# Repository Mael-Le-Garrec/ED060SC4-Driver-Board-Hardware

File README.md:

# ED060SC4 Driver Board

This projects intends to be a SPI driver board for the E-Ink display screen
`ED060SC4`.

This project is still under development, you can have a look at the schematics,
the PCB or the components, but it's not finished and will likely change!

## Schematics

The board is centered around 3 building blocks:

- ED060SC4, EPD screen
- STM32F103C8T6, microcontroller used to drive the screen
- TPS65185, used to generate the different rails required

The schematics can be found in [pdf](./outputs/schematics/ED060SC4_SPI_driver_board.pdf).

## Interactive Board

The PCB, nets and BOM can be seen in an [interactive html format](http://htmlpreview.github.io/?https://raw.githubusercontent.com/Mael-Le-Garrec/ED060SC4-Driver-Board-Hardware/master/outputs/html/ibom.html).

## Gerbers

The gerber files are available in a [zip archive](./outputs/gerbers/gerbers.zip)
ready to be sent for manufacturing.

## Images

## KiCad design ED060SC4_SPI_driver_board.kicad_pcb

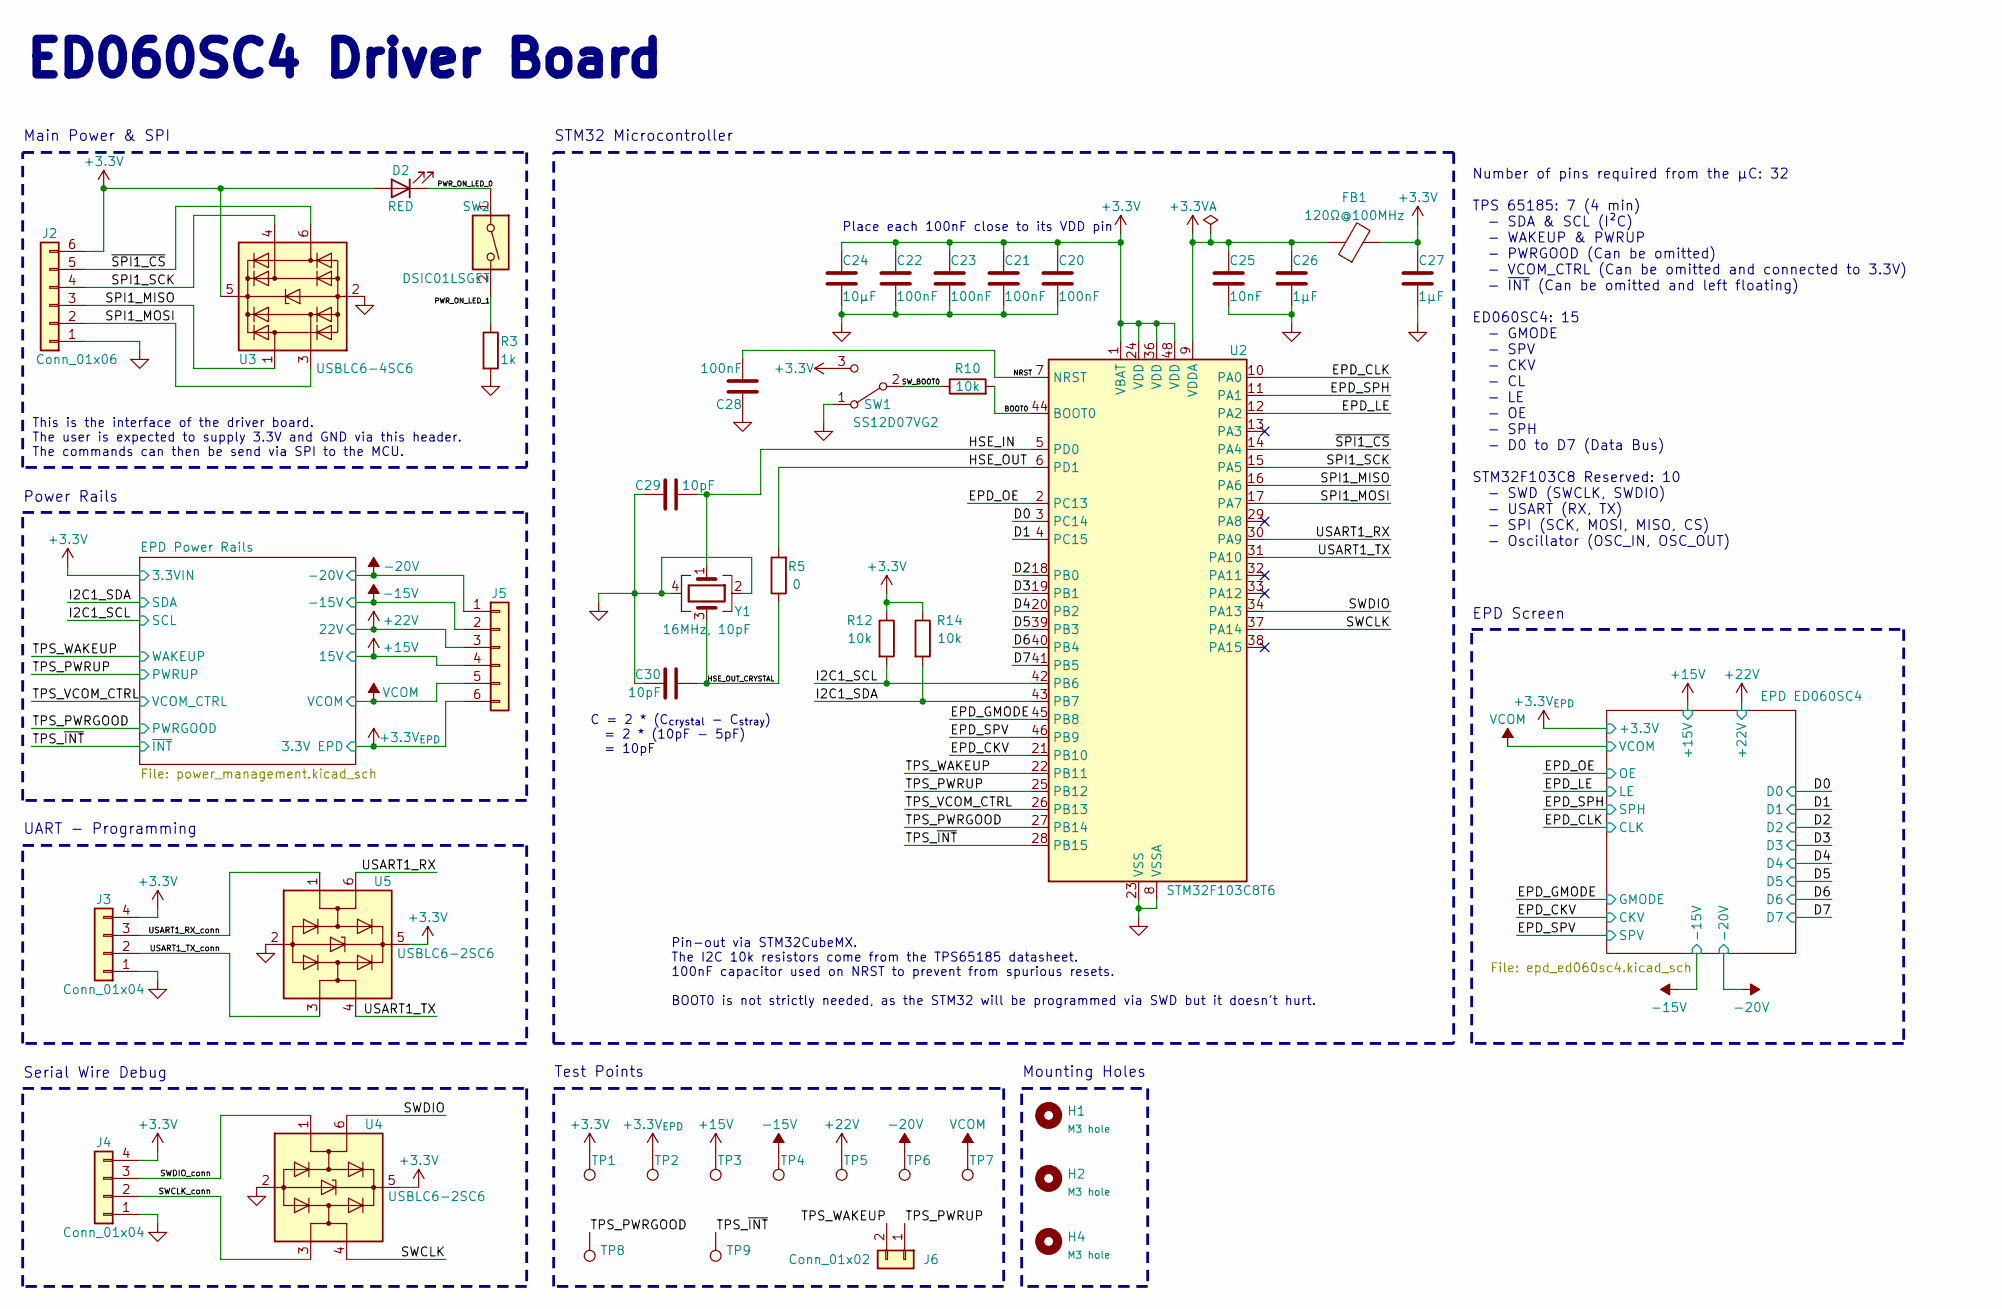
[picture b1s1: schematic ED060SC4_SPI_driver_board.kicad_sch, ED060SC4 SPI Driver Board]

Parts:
C20, C21, C22, C23, C28: 100nF; C_0603_1608Metric; LCSC Part # C1591
C24: 10µF; C_0603_1608Metric; LCSC Part # C85713
C25: 10nF; C_0603_1608Metric; LCSC Part # C1589
C26, C27: 1µF; C_0603_1608Metric; LCSC Part # C5673
C29, C30: 10pF; C_0603_1608Metric; LCSC Part # C1634
D2: RED; LED_0603_1608Metric; LCSC Part # C434419
FB1: 120Ω@100MHz; R_0603_1608Metric; LCSC Part # C14709
H1, H2, H4: M3 hole; MountingHole_2.2mm_M2
J2: Conn_01x06; PinHeader_1x06_P2.54mm_Vertical
J3, J4: Conn_01x04; PinSocket_1x04_P2.54mm_Vertical
J5: Conn_01x06; PinSocket_1x06_P2.54mm_Vertical
J6: Conn_01x02; PinSocket_1x02_P2.54mm_Vertical
R3: 1k; R_0603_1608Metric; LCSC Part # C22548
R5: 0; R_0603_1608Metric; LCSC Part # C103196
R10, R12, R14: 10k; R_0603_1608Metric; LCSC Part # C98220
SW1: SS12D07VG2; SW_SS12D07VG4; LCSC Part # C2939724
SW2: DSIC01LSGET; LCSC Part # C54948
TP1, TP2, TP3, TP4, TP5, TP6, TP7, TP8, TP9: TestPoint; TestPoint_Pad_D1.0mm
U2: STM32F103C8T6; LQFP-48_7x7mm_P0.5mm; LCSC Part # C8734
U3: USBLC6-4SC6; SOT-23-6; LCSC Part # C5197386
U4, U5: USBLC6-2SC6; SOT-23-6; LCSC Part # C2827654
Y1: 16MHz, 10pF; Crystal_SMD_3225-4Pin_3.2x2.5mm; LCSC Part # C112972

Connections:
+3.3V: C20.1, C21.1, C22.1, C23.1, C24.1, C27.1, D2.2 (A), FB1.2, J2.6, J3.4, J4.4, R12.1, R14.1, SW1.3 (C), TP1.1, U2.1 (VBAT), U2.24 (VDD), U2.36 (VDD), U2.48 (VDD), U3.5 (VBUS), U4.5 (VBUS), U5.5 (VBUS); also elsewhere on the board
+3.3VA: C25.1, C26.1, FB1.1, U2.9 (VDDA)
+15V: J5.4, TP3.1; also elsewhere on the board
+22V: J5.3, TP5.1; also elsewhere on the board
-15V: J5.2, TP4.1; also elsewhere on the board
-20V: J5.1, TP6.1; also elsewhere on the board
/BOOT0: R10.2, U2.44 (BOOT0)
/D0: U2.3 (PC14); also elsewhere on the board
/D1: U2.4 (PC15); also elsewhere on the board
/D2: U2.18 (PB0); also elsewhere on the board
/D3: U2.19 (PB1); also elsewhere on the board
/D4: U2.20 (PB2); also elsewhere on the board
/D5: U2.39 (PB3); also elsewhere on the board
/D6: U2.40 (PB4); also elsewhere on the board
/D7: U2.41 (PB5); also elsewhere on the board
/EPD_CKV: U2.21 (PB10); also elsewhere on the board
/EPD_CLK: U2.10 (PA0); also elsewhere on the board
/EPD_GMODE: U2.45 (PB8); also elsewhere on the board
/EPD_LE: U2.12 (PA2); also elsewhere on the board
/EPD_OE: U2.2 (PC13); also elsewhere on the board
/EPD_SPH: U2.11 (PA1); also elsewhere on the board
/EPD_SPV: U2.46 (PB9); also elsewhere on the board
/HSE_IN: C29.2, U2.5 (PD0), Y1.1
/HSE_OUT: R5.2, U2.6 (PD1)
/HSE_OUT_CRYSTAL: C30.2, R5.1, Y1.3
/I2C1_SCL: R12.2, U2.42 (PB6); also elsewhere on the board
/I2C1_SDA: R14.2, U2.43 (PB7); also elsewhere on the board
/NRST: C28.2, U2.7 (NRST)
/PWR_ON_LED_0: D2.1 (K), SW2.1
/PWR_ON_LED_1: R3.1, SW2.2
/SPI1_MISO: J2.3, U2.16 (PA6), U3.1 (I/O1)
/SPI1_MOSI: J2.2, U2.17 (PA7), U3.3 (I/O2)
/SPI1_SCK: J2.4, U2.15 (PA5), U3.4 (I/O3)
/SWCLK: U2.37 (PA14), U4.4 (I/O2)
/SWCLK_conn: J4.2, U4.3 (I/O2)
/SWDIO: U2.34 (PA13), U4.6 (I/O1)
/SWDIO_conn: J4.3, U4.1 (I/O1)
/SW_BOOT0: R10.1, SW1.2 (B)
/TPS_PWRGOOD: TP8.1, U2.27 (PB14); also elsewhere on the board
/TPS_PWRUP: J6.1, U2.25 (PB12); also elsewhere on the board
/TPS_VCOM_CTRL: U2.26 (PB13); also elsewhere on the board
/TPS_WAKEUP: J6.2, U2.22 (PB11); also elsewhere on the board
/TPS_~INT: TP9.1, U2.28 (PB15); also elsewhere on the board
/USART1_RX: U2.30 (PA9), U5.6 (I/O1)
/USART1_RX_conn: J3.3, U5.1 (I/O1)
/USART1_TX: U2.31 (PA10), U5.4 (I/O2)
/USART1_TX_conn: J3.2, U5.3 (I/O2)
/~SPI1_CS: J2.5, U2.14 (PA4), U3.6 (I/O4)
GND: C20.2, C21.2, C22.2, C23.2, C24.2, C25.2, C26.2, C27.2, C28.1, C29.1, C30.1, J2.1, J3.1, J4.1, R3.2, SW1.1 (A), U2.8 (VSSA), U2.23 (VSS), U2.35 (VSS), U2.47 (VSS), U3.2 (GND), U4.2 (GND), U5.2 (GND), Y1.2, Y1.4; also elsewhere on the board

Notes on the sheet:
Number of pins required from the µC: 32 TPS 65185: 7 (4 min) - SDA & SCL (I²C) - WAKEUP & PWRUP - PWRGOOD (Can be omitted) - VCOM_CTRL (Can be omitted and connected to 3.3V) - ~{INT} (Can be omitted and left floating) ED060SC4: 15 - GMODE - SPV - CKV - CL - LE - OE - SPH - D0 to D7 (Data Bus) STM32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
Pin-out via STM32CubeMX. The I2C 10k resistors come from the TPS65185 datasheet. 100nF capacitor used on NRST to prevent from spurious resets. BOOT0 is not strictly needed, as the STM32 will be programmed via SWD but it doesn't hurt.
EPD Screen
STM32 Microcontroller
Main Power & SPI
Power Rails
This is the interface of the driver board. The user is expected to supply 3.3V and GND via this header. The commands can then be send via SPI to the MCU.
Place each 100nF close to its VDD pin
ED060SC4 Driver Board
Serial Wire Debug
Test Points
C = 2 * (C_{crystal} - C_{stray}) = 2 * (10pF - 5pF) = 10pF
UART - Programming
Mounting Holes

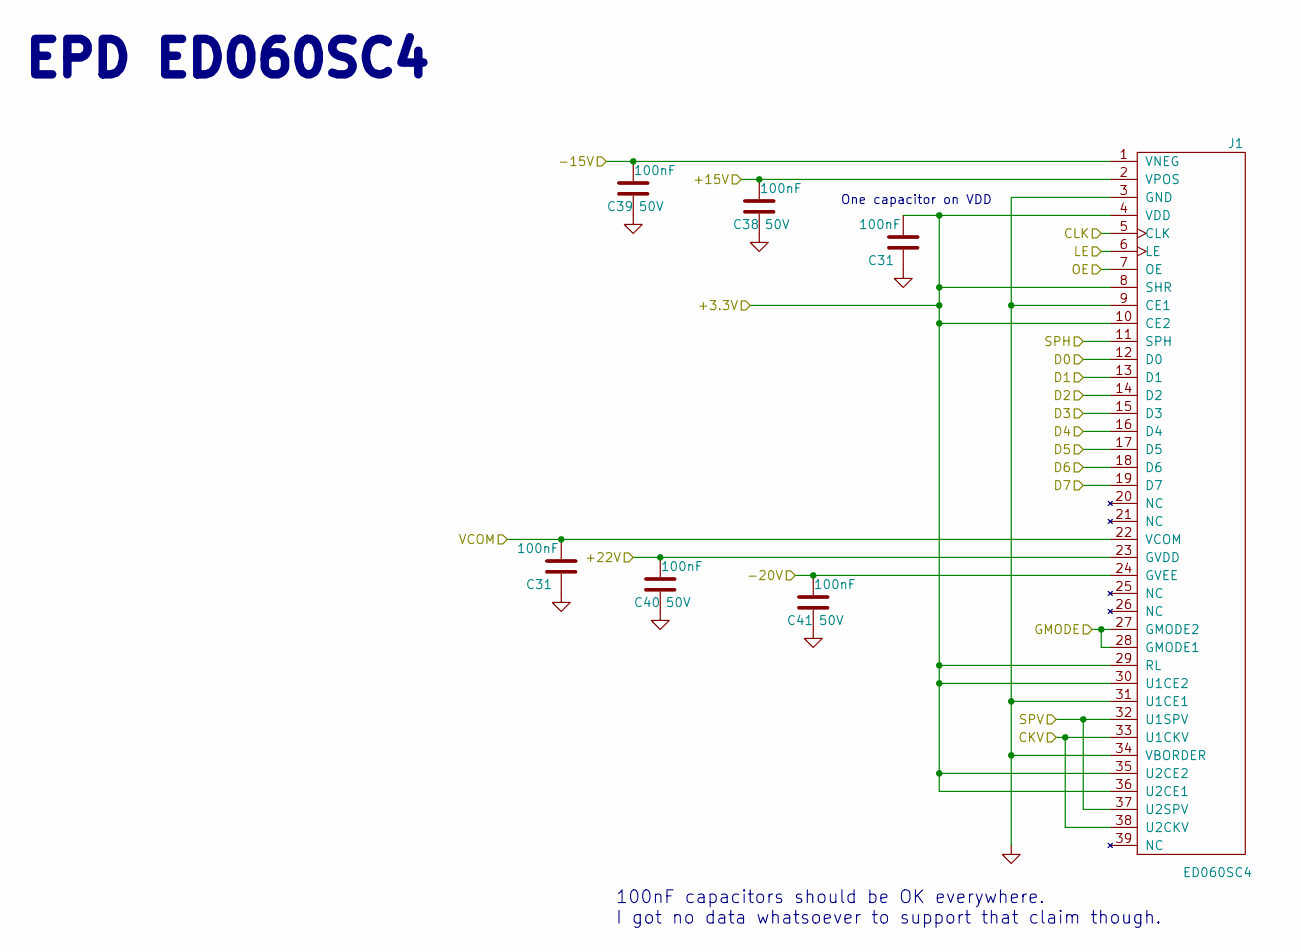
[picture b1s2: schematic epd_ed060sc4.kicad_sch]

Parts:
C31: 100nF; C_0603_1608Metric; LCSC Part # C1591
C38, C39, C40, C41: 100nF; C_0603_1608Metric; Voltage 50V; LCSC Part # C1591
J1: ED060SC4; HRS_FH26W-39S-0.3SHW(60); LCSC Part # C92280

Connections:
+15V: C38.1, J1.2 (VPOS); also elsewhere on the board
+22V: C40.1, J1.23 (GVDD); also elsewhere on the board
-15V: C39.1, J1.1 (VNEG); also elsewhere on the board
-20V: C41.1, J1.24 (GVEE); also elsewhere on the board
/D0: J1.12 (D0); also elsewhere on the board
/D1: J1.13 (D1); also elsewhere on the board
/D2: J1.14 (D2); also elsewhere on the board
/D3: J1.15 (D3); also elsewhere on the board
/D4: J1.16 (D4); also elsewhere on the board
/D5: J1.17 (D5); also elsewhere on the board
/D6: J1.18 (D6); also elsewhere on the board
/D7: J1.19 (D7); also elsewhere on the board
/EPD_CKV: J1.33 (U1CKV), J1.38 (U2CKV); also elsewhere on the board
/EPD_CLK: J1.5 (CLK); also elsewhere on the board
/EPD_GMODE: J1.27 (GMODE2), J1.28 (GMODE1); also elsewhere on the board
/EPD_LE: J1.6 (LE); also elsewhere on the board
/EPD_OE: J1.7 (OE); also elsewhere on the board
/EPD_SPH: J1.11 (SPH); also elsewhere on the board
/EPD_SPV: J1.32 (U1SPV), J1.37 (U2SPV); also elsewhere on the board
GND: C31.2, C38.2, C39.2, C40.2, C41.2, J1.3 (GND), J1.9 (CE1), J1.31 (U1CE1), J1.34 (VBORDER); also elsewhere on the board

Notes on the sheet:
100nF capacitors should be OK everywhere. I got no data whatsoever to support that claim though.
One capacitor on VDD
EPD ED060SC4

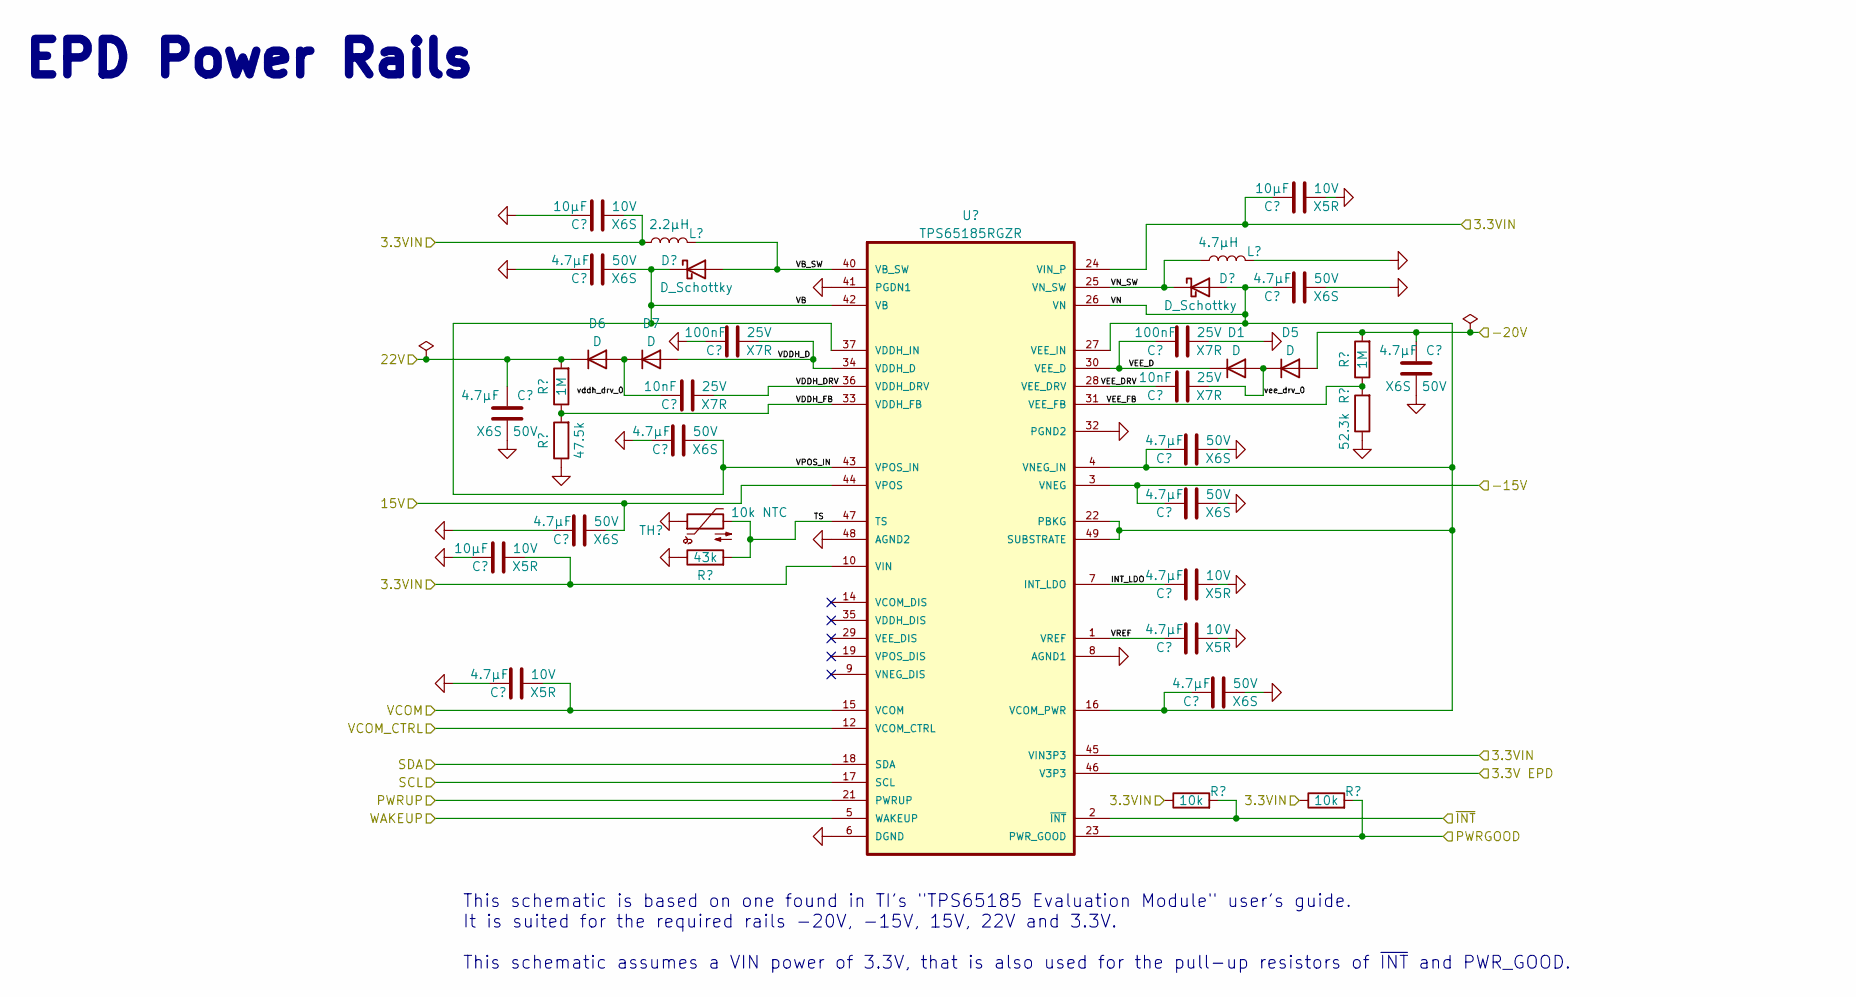
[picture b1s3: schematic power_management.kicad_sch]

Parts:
C1, C4, C6, C8, C10, C11, C14, C18, C19: 4.7µF; C_0805_2012Metric; Voltage 50V; LCSC Part # C98192
C2, C5, C17: 10µF; C_0603_1608Metric; Voltage 10V; LCSC Part # C85713
C3, C12, C13: 4.7µF; C_0805_2012Metric; Voltage 10V; LCSC Part # C98192
C7, C15: 10nF; C_0603_1608Metric; Voltage 25V; LCSC Part # C1589
C9, C16: 100nF; C_0603_1608Metric; Voltage 25V; LCSC Part # C1591
D1, D5, D6, D7: D; D_SOD-123; LCSC Part # C82544
D3, D4: D_Schottky; D_SOD-123; LCSC Part # C82544
L1: 2.2µH; TDK_VLS252015ET-2R2M; LCSC Part # C136232
L2: 4.7µH; L_Taiyo-Yuden_NR-40xx; LCSC Part # C92936
R1, R8: 1M; R_0603_1608Metric; LCSC Part # C105578
R2: 47.5k; R_0603_1608Metric; LCSC Part # C137715
R4: 43k; R_0603_1608Metric; LCSC Part # C137719
R6, R7: 10k; R_0603_1608Metric; LCSC Part # C98220
R9: 52.3k; R_0603_1608Metric; LCSC Part # C185323
TH1: 10k NTC; R_0603_1608Metric; LCSC Part # C13564
U1: TPS65185RGZR; QFN50P700X700X100-49N; LCSC Part # C139291

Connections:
+3.3V: C2.1, C5.2, C17.2, L1.1, R6.1, R7.1, U1.10 (VIN), U1.24 (VIN_P), U1.45 (VIN3P3); also elsewhere on the board
+15V: C4.1, U1.44 (VPOS); also elsewhere on the board
+22V: C1.2, D6.1 (K), R1.2; also elsewhere on the board
-15V: C11.1, U1.3 (VNEG); also elsewhere on the board
-20V: C19.2, D5.2 (A), R8.2; also elsewhere on the board
/EPD Power Rails/INT_LDO: C12.1, U1.7 (INT_LDO)
/EPD Power Rails/TS: R4.2, TH1.2, U1.47 (TS)
/EPD Power Rails/VB: C6.2, C8.2, D3.1 (K), U1.37 (VDDH_IN), U1.42 (VB), U1.43 (VPOS_IN)
/EPD Power Rails/VB_SW: D3.2 (A), L1.2, U1.40 (VB_SW)
/EPD Power Rails/VDDH_D: C9.2, D7.2 (A), U1.34 (VDDH_D)
/EPD Power Rails/VDDH_DRV: C7.2, U1.36 (VDDH_DRV)
/EPD Power Rails/VDDH_FB: R1.1, R2.2, U1.33 (VDDH_FB)
/EPD Power Rails/VEE_D: C16.2, D1.1 (K), U1.30 (VEE_D)
/EPD Power Rails/VEE_DRV: C15.1, U1.28 (VEE_DRV)
/EPD Power Rails/VEE_FB: R8.1, R9.2, U1.31 (VEE_FB)
/EPD Power Rails/VN: C10.1, C14.1, C18.2, D4.2 (A), U1.4 (VNEG_IN), U1.16 (VCOM_PWR), U1.22 (PBKG), U1.26 (VN), U1.27 (VEE_IN), U1.49 (SUBSTRATE)
/EPD Power Rails/VN_SW: D4.1 (K), L2.2, U1.25 (VN_SW)
/EPD Power Rails/VREF: C13.1, U1.1 (VREF)
/EPD Power Rails/vddh_drv_0: C7.1, D6.2 (A), D7.1 (K)
/EPD Power Rails/vee_drv_0: C15.2, D1.2 (A), D5.1 (K)
/I2C1_SCL: U1.17 (SCL); also elsewhere on the board
/I2C1_SDA: U1.18 (SDA); also elsewhere on the board
/TPS_PWRGOOD: R7.2, U1.23 (PWR_GOOD); also elsewhere on the board
/TPS_PWRUP: U1.21 (PWRUP); also elsewhere on the board
/TPS_VCOM_CTRL: U1.12 (VCOM_CTRL); also elsewhere on the board
/TPS_WAKEUP: U1.5 (WAKEUP); also elsewhere on the board
/TPS_~INT: R6.2, U1.2 (~INT); also elsewhere on the board
GND: C1.1, C2.2, C3.2, C4.2, C5.1, C6.1, C8.1, C9.1, C10.2, C11.2, C12.2, C13.2, C14.2, C16.1, C17.1, C18.1, C19.1, L2.1, R2.1, R4.1, R9.1, TH1.1, U1.6 (DGND), U1.8 (AGND1), U1.32 (PGND2), U1.41 (PGDN1), U1.48 (AGND2); also elsewhere on the board

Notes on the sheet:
This schematic is based on one found in TI's "TPS65185 Evaluation Module" user's guide. It is suited for the required rails -20V, -15V, 15V, 22V and 3.3V. This schematic assumes a VIN power of 3.3V, that is also used for the pull-up resistors of ~{INT} and PWR_GOOD.
EPD Power Rails

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
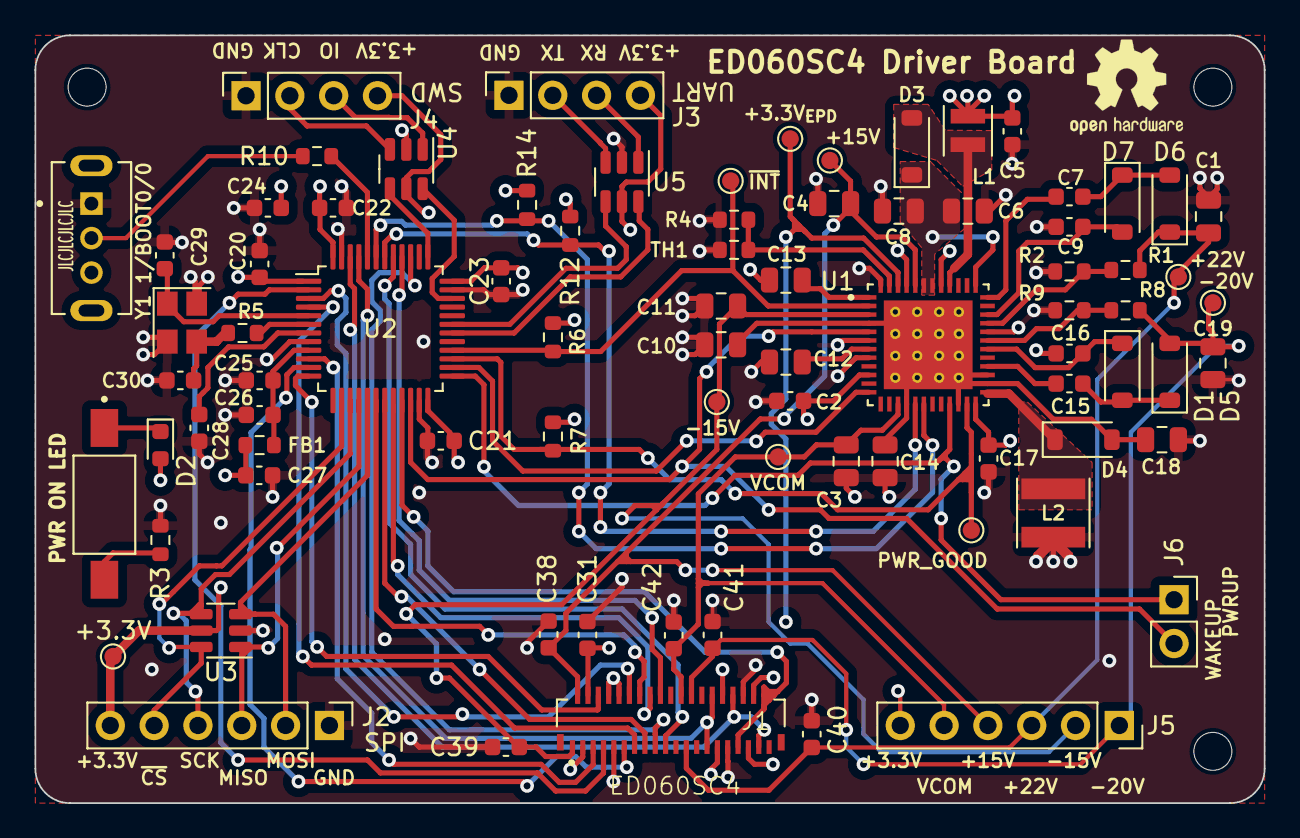
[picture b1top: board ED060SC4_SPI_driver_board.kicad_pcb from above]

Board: 4 copper layers, 71.2 x 44.5 mm, 85 parts (0 on the bottom side), 66 nets.

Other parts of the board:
C42: 100nF; C_0603_1608Metric

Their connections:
GND: C42.2; also elsewhere on the board

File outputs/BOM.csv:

"Reference","Value","Footprint","LCSC Part #","Type","Voltage","Qty"
"C1, C4, C6, C8, C10, C11, C14, C18, C19","4.7µF","Capacitor_SMD:C_0805_2012Metric","C98192","X6S","50V","9"
"C2, C17","10µF","Capacitor_SMD:C_0603_1608Metric","C85713","X5R","10V","2"
"C3, C12, C13","4.7µF","Capacitor_SMD:C_0805_2012Metric","C98192","X5R","10V","3"
"C5","10µF","Capacitor_SMD:C_0603_1608Metric","C85713","X6S","10V","1"
"C7, C15","10nF","Capacitor_SMD:C_0603_1608Metric","C1589","X7R","25V","2"
"C9, C16","100nF","Capacitor_SMD:C_0603_1608Metric","C1591","X7R","25V","2"
"C20-C23, C28, C31, C42","100nF","Capacitor_SMD:C_0603_1608Metric","C1591","","","7"
"C24","10µF","Capacitor_SMD:C_0603_1608Metric","C85713","","","1"
"C25","10nF","Capacitor_SMD:C_0603_1608Metric","C1589","","","1"
"C26, C27","1µF","Capacitor_SMD:C_0603_1608Metric","C5673","","","2"
"C29, C30","10pF","Capacitor_SMD:C_0603_1608Metric","C1634","","","2"
"C38-C41","100nF","Capacitor_SMD:C_0603_1608Metric","C1591","","50V","4"
"D1, D5-D7","D","Diode_SMD:D_SOD-123","C82544","","","4"
"D2","RED","LED_SMD:LED_0603_1608Metric","C82544","","","1"
"D3, D4","D_Schottky","Diode_SMD:D_SOD-123","C82544","","","2"
"FB1","120Ω@100MHz","Resistor_SMD:R_0603_1608Metric","C14709","","","1"
"H1, H2, H4","M3 hole","MountingHole:MountingHole_2.2mm_M2","","","","3"
"J1","ED060SC4","local_lib:HRS_FH26W-39S-0.3SHW(60)","C92280","","","1"
"J2","Conn_01x06","Connector_PinHeader_2.54mm:PinHeader_1x06_P2.54mm_Vertical","","","","1"
"J3, J4","Conn_01x04","Connector_PinSocket_2.54mm:PinSocket_1x04_P2.54mm_Vertical","","","","2"
"J5","Conn_01x06","Connector_PinSocket_2.54mm:PinSocket_1x06_P2.54mm_Vertical","","","","1"
"J6","Conn_01x02","Connector_PinSocket_2.54mm:PinSocket_1x02_P2.54mm_Vertical","","","","1"
"L1","2.2µH","local_lib:TDK_VLS252015ET-2R2M","C136232","","","1"
"L2","4.7µH","Inductor_SMD:L_Taiyo-Yuden_NR-40xx","C92936","","","1"
"R1, R8","1M","Resistor_SMD:R_0603_1608Metric","C105578","","","2"
"R2","47.5k","Resistor_SMD:R_0603_1608Metric","C137715","","","1"
"R3","1k","Resistor_SMD:R_0603_1608Metric","C22548","","","1"
"R4","43k","Resistor_SMD:R_0603_1608Metric","C137719","","","1"
"R5","0","Resistor_SMD:R_0603_1608Metric","C103196","","","1"
"R6, R7, R10, R12, R14","10k","Resistor_SMD:R_0603_1608Metric","C98220","","","5"
"R9","52.3k","Resistor_SMD:R_0603_1608Metric","C185323","","","1"
"SW1","SS12D07VG2","local_lib:SW_SS12D07VG4","C2939724","","","1"
"SW2","DSIC01LSGET","local_lib:DSIC01LSGET","C54948","","","1"
"TH1","10k NTC","Resistor_SMD:R_0603_1608Metric","C13564","","","1"
"TP1-TP9","TestPoint","TestPoint:TestPoint_Pad_D1.0mm","","","","9"
"U1","TPS65185RGZR","local_lib:QFN50P700X700X100-49N","C139291","","","1"
"U2","STM32F103C8T6","Package_QFP:LQFP-48_7x7mm_P0.5mm","C8734","","","1"
"U3","USBLC6-4SC6","Package_TO_SOT_SMD:SOT-23-6","C5197386","","","1"
"U4, U5","USBLC6-2SC6","Package_TO_SOT_SMD:SOT-23-6","C2827654","","","2"
"Y1","16MHz, 10pF","Crystal:Crystal_SMD_3225-4Pin_3.2x2.5mm","C112972","","","1"

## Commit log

2023-04-04 Starting to wire the TPS65185 PMIC
2023-04-10 Wired TPS65185 according to datasheet
2023-04-13 Full Schematic
2023-04-13 Rearrange schematic
2023-04-13 add pdf schematic
2023-04-16 fix paths
2023-04-16 Use DIP switch for power LED
2023-04-16 Update library path and add DIP switch
2023-04-16 fix paths once again
2023-04-16 set value of dip led switch
2023-04-16 Set voltage rating of capacitors
2023-04-16 Add footprints and some labels
2023-04-17 Update TPS65185 based on evaluation module
2023-04-17 Add ESD and SPDT switch
2023-04-17 Update EPD capacitors
2023-04-17 Changed VDDH and VEE capacitors to 4.7µF
    The evaluation board uses 4.7µF capacitors instead of 2.2µF as stated in
    the datasheet.
2023-04-19 Fixed PWR flags in schematic
2023-04-19 Added the thermal pad to the TPS65185
2023-04-19 First rough PCB layout without traces
2023-04-19 Add a connector for easy access to voltages
2023-04-20 PCB routing
2023-04-23 TPS Connector and LCSC part #
2023-04-23 update clearances
2023-04-23 Change D footprint for TPS and LCSC part #
2023-04-23 Remove some capacitors for EPD
2023-04-23 Routed PCB + outputs
2023-04-23 Updated TPS pad for heat dissipation
2023-04-23 Smaller board outline and some silkscreen info
2023-04-23 fix gitignore #
2023-04-23 bigger via holes for TPS heat
2023-04-23 Update outputs
2023-04-23 Update iBOM
2023-04-23 Add a quick README
2023-04-23 fix images link in README
2023-04-24 Add ground pour to external layers
2023-04-24 Add titles to schematics
2023-04-25 Add mounting holes
2023-04-26 add generic 3D model for L1 and L2
2023-04-26 Add mounting holes and connector to Bom (empty)
2023-04-26 Fix LED BOM # and update outputs
2023-04-26 fix LED in iBOM
2023-04-26 add JLC order # text for location
2023-04-29 add svg schematics
2023-04-29 Add VN pad under TPS and fix some typos
2023-05-14 Fix unaligned hole
